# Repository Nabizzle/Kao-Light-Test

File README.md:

# Kao-Light-Test
Scripts for working with the Kao Light Test Model and Hardware

# Table of Contents

* [Getting Started](#getting-started)
  * [Prerequisites](#prerequisites)
* [Running the Code](#running-the-code)
* [Author](#author)
* [Description of Each Script](#description-of-each-script)
  * [panTiltModel.m](#pantiltmodelm)
  
  # Getting Started
  
  As of right now, there is only the modeling code, [panTIltModel.m](#pantiltmodelm), which makes a model of how the laser is controlled. In the future, the code for controlling the Arduino Uno to tilting and panning the read laser mount will be added.
  
  Also included are the Eagle files for making the shield for the Arduino that controlls the servos of the laser mount.
  
  ## Prerequisites
  
  Software:
  
  * [MATLAB 2018 or later](https://www.mathworks.com/help/matlab/) (For the computational model and prefinding tilt and pan angles)
  * [Arduino IDE](https://www.arduino.cc/en/software)
  
  Testing electronics (what is needed is based on the test)
  * Grapevine with micro D to Sub-D cable
  * [Arduino Uno](https://store-usa.arduino.cc/products/arduino-uno-rev3)
  * Arduino Uno Shield

  # Running the Code
  
  When the Arduino code is added, you will need to plug in the shield and the servos and upload the Arduino code to it. You will also need to take the found tilt and pan angles for the grid size that you want and add them to the arduino code. Make sure that there are 4096 tilt values in a single row array.
  Also make sure to plug in the digital output cable from the Grapevine to the shield. This cable sends out the 12 bit digital signal to control for the 4096 angle values and a 13th signal to turn the laser on or off.
  
  # Author

  * **Nabeel Chowdhury** - Initial Creator
  
  # Description of Each Script
  
  ## panTiltModel.m
  Creates a computational model of the laser mount with user definable dimensions. For more information on how the model is made, refer to [this](https://github.com/Nabizzle/Kao-Light-Test/blob/main/docs/supplimentary/Modeling%20Laser%20Mount%20Pan%20and%20Tilt.pdf) supplimentary document.
  The code has 3 modes: debug, finding tilt and pan angles for a grid of points, visualizing the laser hit location of a given command position.
  
  In bebug mode, the laser tries to hit a square grid of points that is as wide as the gird is far away from the laser mount. The distance the mount is from the grid is user definable. The result of the laser mount hitting a 20x20 grid when 200 mm away from the grid is shown below.
  
  The finding angles mode, the user define a recangular grid of points for the model to find tile and pan angles for. This mode also outputs the expected laser hit locations for you to make sure that the code is working correctly.
  
  The final model allows you to set a command position at the top of the code and see that the model is hitting the right grid point.

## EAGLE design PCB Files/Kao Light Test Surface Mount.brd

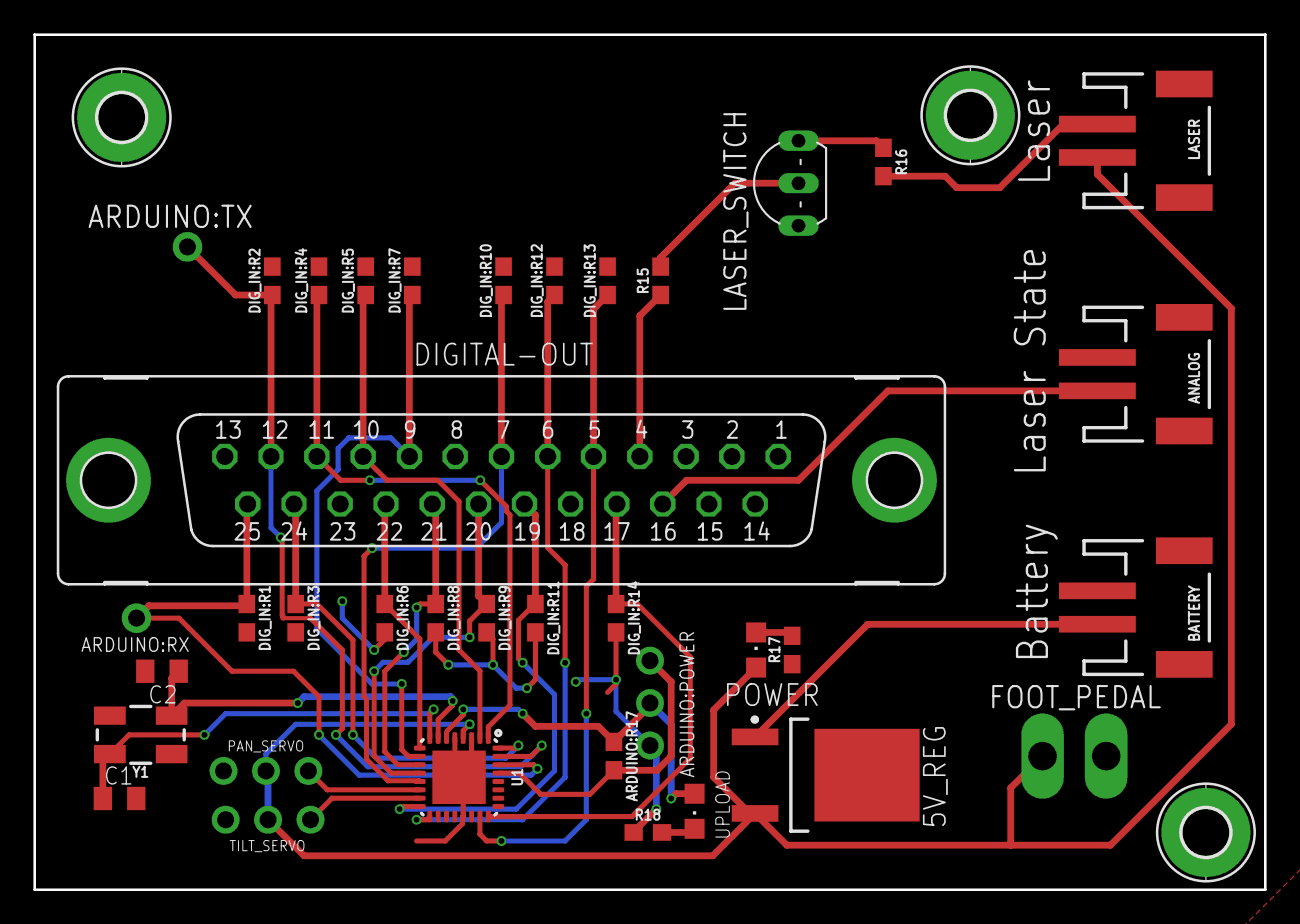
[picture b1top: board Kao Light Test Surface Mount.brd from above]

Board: 2 copper layers, 73.7 x 51.2 mm, 40 parts (0 on the bottom side), 30 nets.

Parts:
5V_REG: UA78M05IKVURG3; KVU0003A_N
ANALOG: JST-2-SMD
ARDUINO:POWER: 1X03-CLEANBIG
ARDUINO:R17: 10k; 0603
ARDUINO:RX: 1X01-CLEANBIG
ARDUINO:TX: 1X01-CLEANBIG
BATTERY: JST-2-SMD
C1, C2: C0805K
DIGITAL-OUT: F25VP
DIG_IN:R1, DIG_IN:R2, DIG_IN:R3, DIG_IN:R4, DIG_IN:R5, DIG_IN:R6, DIG_IN:R7, DIG_IN:R8, DIG_IN:R9, DIG_IN:R10, DIG_IN:R11, DIG_IN:R12, DIG_IN:R13, DIG_IN:R14: 10k; 0603
FOOT_PEDAL: TP2P2-38-17; P2-38-17
H1, H2, H3: MOUNT-PAD-ROUND2.8; 2,8-PAD
LASER: JST-2-SMD
LASER_SWITCH: 2N3904; TO92-EBC-OVAL
PAN_SERVO: 1X03-CLEANBIG
POWER: CHIPLED_0805
R15: 10k; 0603
R16, R17, R18: 220; 0603
TILT_SERVO: 1X03-CLEANBIG
U1: MLF32-PAD
UPLOAD: CHIPLED_0805
Y1: 16MHz; CRYSTAL-SMD-5X3.2-4PAD

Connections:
5VOUT: 5V_REG.3, FOOT_PEDAL.TP-1, LASER.2, PAN_SERVO.2, POWER.A, TILT_SERVO.2, U1.4
BAT+: 5V_REG.1, BATTERY.2
D1: ARDUINO:RX.1, DIGITAL-OUT.25, DIG_IN:R1.1, U1.30
D2: ARDUINO:TX.1, DIGITAL-OUT.12, DIG_IN:R2.1, U1.31
D3: DIGITAL-OUT.24, DIG_IN:R3.1, U1.32
D4: DIGITAL-OUT.11, DIG_IN:R4.1, U1.1
D5: DIGITAL-OUT.10, DIG_IN:R5.1, U1.2
D6: DIGITAL-OUT.22, DIG_IN:R6.1, U1.9
D7: DIGITAL-OUT.9, DIG_IN:R7.1, U1.10
D8: DIGITAL-OUT.21, DIG_IN:R8.1, U1.11
D9: DIGITAL-OUT.20, DIG_IN:R9.1, U1.12
D10: DIGITAL-OUT.7, DIG_IN:R10.1, U1.13
D11: DIGITAL-OUT.19, DIG_IN:R11.1, U1.16
D12: DIGITAL-OUT.6, DIG_IN:R12.1, U1.17
D13: DIGITAL-OUT.5, DIG_IN:R13.1, U1.23
D14: DIGITAL-OUT.17, DIG_IN:R14.1, U1.24
D15: DIGITAL-OUT.4, R15.1
D16: ANALOG.2, DIGITAL-OUT.16
GND: 5V_REG.4, ANALOG.1, ARDUINO:POWER.3, BATTERY.1, C1.2, C2.2, DIGITAL-OUT.1, DIGITAL-OUT.2, DIGITAL-OUT.3, DIGITAL-OUT.8, DIGITAL-OUT.13, DIGITAL-OUT.18, DIGITAL-OUT.23, DIGITAL-OUT.G1, DIGITAL-OUT.G2, DIG_IN:R1.2, DIG_IN:R2.2, DIG_IN:R3.2, DIG_IN:R4.2, DIG_IN:R5.2, DIG_IN:R6.2, DIG_IN:R7.2, DIG_IN:R8.2, DIG_IN:R9.2, DIG_IN:R10.2, DIG_IN:R11.2, DIG_IN:R12.2, DIG_IN:R13.2, DIG_IN:R14.2, FOOT_PEDAL.TP-2, H1.B2,8, H2.B2,8, H3.B2,8, LASER_SWITCH.E, PAN_SERVO.1, R17.1, R18.1, TILT_SERVO.1, U1.3, U1.5, U1.21, U1.PAD
unnamed: C2.1, U1.7, Y1.1
unnamed: LASER_SWITCH.B, R15.2
unnamed: LASER_SWITCH.C, R16.1
unnamed: C1.1, U1.8, Y1.3
unnamed: POWER.C, R17.2
unnamed: LASER.1, R16.2
unnamed: R18.2, UPLOAD.C
PAN: PAN_SERVO.3, U1.14
RESET: ARDUINO:POWER.1, ARDUINO:R17.2, U1.29
TILT: TILT_SERVO.3, U1.15
VIN: ARDUINO:POWER.2, ARDUINO:R17.1, U1.6, UPLOAD.A

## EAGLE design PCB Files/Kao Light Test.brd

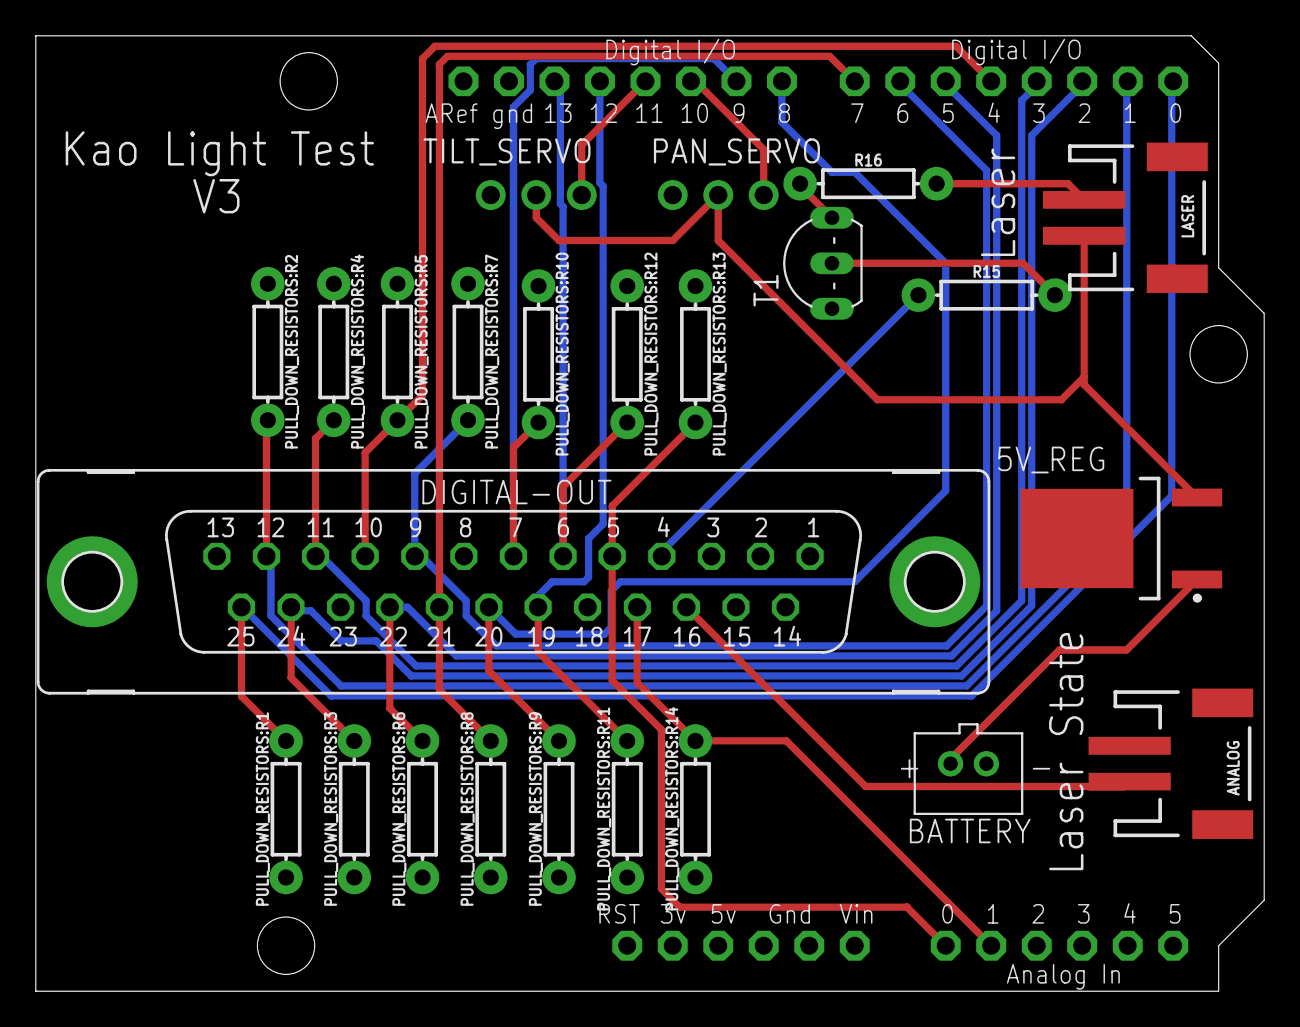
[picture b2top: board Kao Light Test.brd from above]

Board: 2 copper layers, 68.6 x 53.3 mm, 25 parts (0 on the bottom side), 24 nets.

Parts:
5V_REG: UA78M05IKVURG3; KVU0003A_N
ANALOG: JST-2-SMD
BATTERY: JST-PH-2-THM
DIGITAL-OUT: F25VP
LASER: JST-2-SMD
PAN_SERVO: 1X03-CLEANBIG
PULL_DOWN_RESISTORS:R1, PULL_DOWN_RESISTORS:R2, PULL_DOWN_RESISTORS:R3, PULL_DOWN_RESISTORS:R4, PULL_DOWN_RESISTORS:R5, PULL_DOWN_RESISTORS:R6, PULL_DOWN_RESISTORS:R7, PULL_DOWN_RESISTORS:R8, PULL_DOWN_RESISTORS:R9, PULL_DOWN_RESISTORS:R10, PULL_DOWN_RESISTORS:R11, PULL_DOWN_RESISTORS:R12, PULL_DOWN_RESISTORS:R13, PULL_DOWN_RESISTORS:R14: 10k; AXIAL-0.3
R15: 10k; AXIAL-0.3
R16: 220; AXIAL-0.3
T1: 2N2222; TO92-EBC-OVAL
TILT_SERVO: 1X03-CLEANBIG
U$1: ARDUINOUNO; ARDUINO

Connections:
5VOUT: 5V_REG.3, LASER.2, PAN_SERVO.2, TILT_SERVO.2
BAT+: 5V_REG.1, BATTERY.1
D1: DIGITAL-OUT.25, PULL_DOWN_RESISTORS:R1.P$2, U$1.D0
D2: DIGITAL-OUT.12, PULL_DOWN_RESISTORS:R2.P$2, U$1.D1
D3: DIGITAL-OUT.24, PULL_DOWN_RESISTORS:R3.P$2, U$1.D2
D4: DIGITAL-OUT.11, PULL_DOWN_RESISTORS:R4.P$2, U$1.D3
D5: DIGITAL-OUT.10, PULL_DOWN_RESISTORS:R5.P$2, U$1.D4
D6: DIGITAL-OUT.22, PULL_DOWN_RESISTORS:R6.P$2, U$1.D5
D7: DIGITAL-OUT.9, PULL_DOWN_RESISTORS:R7.P$2, U$1.D6
D8: DIGITAL-OUT.21, PULL_DOWN_RESISTORS:R8.P$2, U$1.D7
D9: DIGITAL-OUT.20, PULL_DOWN_RESISTORS:R9.P$2, U$1.D8
D10: DIGITAL-OUT.7, PULL_DOWN_RESISTORS:R10.P$2, U$1.D9
D11: DIGITAL-OUT.19, PULL_DOWN_RESISTORS:R11.P$2, U$1.D12
D12: DIGITAL-OUT.6, PULL_DOWN_RESISTORS:R12.P$2, U$1.D13
D13: DIGITAL-OUT.5, PULL_DOWN_RESISTORS:R13.P$2, U$1.A0
D14: DIGITAL-OUT.17, PULL_DOWN_RESISTORS:R14.P$2, U$1.A1
D15: DIGITAL-OUT.4, R15.P$1
D16: ANALOG.2, DIGITAL-OUT.16
GND_1: 5V_REG.4, ANALOG.1, BATTERY.2, DIGITAL-OUT.1, DIGITAL-OUT.2, DIGITAL-OUT.3, DIGITAL-OUT.8, DIGITAL-OUT.13, DIGITAL-OUT.18, DIGITAL-OUT.23, DIGITAL-OUT.G1, DIGITAL-OUT.G2, PAN_SERVO.1, PULL_DOWN_RESISTORS:R1.P$1, PULL_DOWN_RESISTORS:R2.P$1, PULL_DOWN_RESISTORS:R3.P$1, PULL_DOWN_RESISTORS:R4.P$1, PULL_DOWN_RESISTORS:R5.P$1, PULL_DOWN_RESISTORS:R6.P$1, PULL_DOWN_RESISTORS:R7.P$1, PULL_DOWN_RESISTORS:R8.P$1, PULL_DOWN_RESISTORS:R9.P$1, PULL_DOWN_RESISTORS:R10.P$1, PULL_DOWN_RESISTORS:R11.P$1, PULL_DOWN_RESISTORS:R12.P$1, PULL_DOWN_RESISTORS:R13.P$1, PULL_DOWN_RESISTORS:R14.P$1, T1.E, TILT_SERVO.1, U$1.GND, U$1.GND1
unnamed: R15.P$2, T1.B
unnamed: R16.P$1, T1.C
unnamed: LASER.1, R16.P$2
PAN: PAN_SERVO.3, U$1.D10
TILT: TILT_SERVO.3, U$1.D11

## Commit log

2021-09-11 Adds the initial files
    Adds the .gitignore file and the initial file that compute the correct
    tilt angle when there is no pan.
2021-09-11 feat: Adds code to find pan angle
    Also adds code to record a video testing the angle choices on hitting a
    grid.
2021-09-11 feat: deletes the video writter code
2021-09-11 docs: Adds debug video to docs folder
2021-09-11 feat: Adds debug and find angles flags
    The code now has a debug mode and a mode that finds all of the angles to
    hit a specific size grid with a given resolution
2021-09-11 docs: Adds files to describing tilt and pan calc
    Makes a LaTeX doc with figures to describe how the tilt and pan angles
    are found.
2021-09-11 feat: Adds functionality to code that finds angles
    The code how finds angles for a 5mm rectangular grid and also has code
    that outputs the locations where the model expects the laser to hit the
    target.
2021-09-12 docs: Updated suplimentary doc about modeling
2021-09-12 fix: fixes gitignore file
    The gitignore file was named incorrectly
2021-09-12 feat: Adds switch case to modes
    Eliminates the if else statements in favor of a switch statement. NOTE,
    there is still a bug in mode 2 for finidng angles
2021-09-12 fix: Fixed syntax errors
    Ran through each mode and fixed errors that came up. Also, fixed a bug
    where the find angles code did not reach the right most points.
2021-09-12 docs: Adds a gif version of the debug video
2021-09-12 Rename panTIltModel.m to panTiltModel.m
2021-09-12 docs: Adds Images of Arduino Shield
2021-09-12 docs: Creates initial ReadMe
2021-09-12 docs: Moves ReadMe to docs folder
2021-09-12 fix: fixes the end of the grid X array for loop
2021-09-12 feat: Updates .gitignore for Eagle Files
2021-09-12 move: Moves code to a Code directory
2021-09-12 docs: Adds an SVG file for the target grid
    The grid is colored in case you want to laser cut it and engrave the
    grid
2021-09-12 feat: Adds the Eagle files
2022-03-26 feat: Creates a debug script for the foot pedal
    Closes #5
2022-03-26 feat: Convert the graph to volts
2022-03-26 feat; Adds a debug script for the digital output
    Closes #6
2022-03-26 feat: Adds gitingore file for Matlab files
2022-03-26 feat: Adds script to convert digital signal to num
    Adds a debug script for finding the base 10 number from the input
    digital signals. NOTE that the first two outputs are always set to their
    values since they are also used for the serial monitor. They should work
    when commanding the servos.
    Closes #2
2022-03-26 fix: Changes the model to only have 400 points
    The lowered number of points to to account for the arduino's memory
2022-03-26 feat: Creates the script to control the servos
    Adds an arduino script to take in the digital outputs of the Grapevine
    and move the servo to desired positions based on the computational model
    Closes #7
2022-03-26 fix: Changes the model to fit the real dimensions
    Changes the model and the arrays of found positions to match the real
    dimensions of the testing setup
2022-03-26 feat: Creates app and servo angle finder function
    Crates the code to find the servo angles and lets the experimentor
    examine them. Also outputs the variables to the workspace in case the
    user wants to copy over the angles to the arduino.
    Closes #8
2022-03-26 feat: Adds a function to test the laser
    Adds a laser toggle and a function to determine where the laser will hit
    with its various tilt angles
2022-03-26 feat: Adds a function to pan the laser at tilt
    Adds a function to pan the laser at the current tilt angle.
    Closes #1
2022-03-27 feat: Adds experiment recording script
    Adds the script to iterate through each point along the desired tilt
    angle. The script also take in the number of repeated trials from a GUI
    element and saves out the data for analysis afterwards.
    Closes #3
2022-03-28 feat: Adds Test stop and Validates code
    Adds a lamp to indicate when the test is running, a stop test button,
    and validates that all parts of the test work at least without a
    subject. The code also now saves out the servo angles used for the test
    which it needed to previously, but I forgot to add.
    Closes #10
2022-03-28 fix: Turns on the laser in the laser sweep code
    The laser did not actually turn on in the laser sweep code. Also
    shortens the time between each pan angle in the laser sweep.
2022-03-28 docs: Adds an image of the testing app.
2022-03-28 fix: Adds a white background the the app image
2022-03-28 docs: Updates ReadMe to be up to date with v2.1.1
2022-03-29 fix: Addresses error in the main test
    The laser didn't turn on in the test since the laser state indicator
    would turn off the parallel port. Now, both turn on together.
2022-03-29 fix: Removes the displayed output from the sweep
2022-03-31 feat: Adds the data analysis code
    Adds code to analyze the prelim data. This code needs to be refined and
    added to the app.
    Closes #4
2022-03-31 docs: Updates ReadMe with data analysis scripts
    Also fixes alphabetical order of script descriptions
2022-09-15 feat: Saves a list of test angles
    App now allows the user to save a list of tilt angles for the test as
    well as manually edit or delete elements of the list. The current code
    allows duplicate entries, but that could be eliminated if undesired.
    Closes #14 issue.
2022-09-19 feat: updates PCB
    Adds changes from Issue #9
2022-09-19 BREAKING CHANGE feat: Grapevine to controls angle
    Changes code so that the first seven digital outputs of the Grapevine
    control the pan angle of the laser and the last 5 digital outputs
    control the tilt angle. The rest of the functions are updated
    accordingly. For example all code to calculate angles was been deleted
    and the functions that refered to the calculated angles have been
    updated to use the new angle formats. Also added a Guage for test
2022-09-19 feat: Updates the look of the GUI
    Makes the laser toggle a toggle switch and updates the start button
    color
2022-09-19 chore: Updates look of Gui
    Updates the tick labels of the pan and tilt sliders to be more logical
    numbers.
2022-09-20 feat: Grapevine controls pan and tilt angles
    The arduino takes the 12 digital inputs from the Grapevine and converts
    the first 7 into 128 different pan angles and the last 5 inputs as 32
    different tilt angles. The pan and tilt angles range around the center
    of their range of motion.
    Closes #11 and closes #13 issues.
2022-09-21 docs: Updates ReadMe with the changes to the Gui
2022-09-21 fix: Adjusts the pan and tilt sliders numbering
    The sliders and table now accurately show the pan and tilt angles in
    degrees. Extra variables were also eliminated and the GUI image in the
    ReadMe was updated.
2022-09-21 chore: Updates the code for new laser state output
    Switches the output from the first SMA to the 14th output of the microD
    connector
2022-09-21 feat: Improves the look of the PCB
    Improves the naming and clenliness of the PCB
2022-09-21 docs: Updates the ReadMe with the new PCB design.
2022-09-21 docs: Adds name of test to PCB
2022-09-21 feat: Grounds the Cable's housing.
    Also updates the images in the ReadMe
2022-09-22 docs: Adds note to the ReadMe on flashing scripts
    Adds a note that the arduino shield must be disconnected from the
    arduino when flashing a new script as the pull-down resistors on digital
    inputs 0 and 1 prevent the upload process from occurring. This is also
    why the Serial monitor does not work properly with the shield for these
    pins.
2022-09-22 docs: Updates the PCB and ReadMe to be clearer
    The PCB was updated so that the servos are labeled as what they are
    instead of as numbers. One resistor was also updated and all other
    digital grounds were connected to the ground plane.
2022-09-22 fix: Corrects logic in code
    Corrects how the arduino interprets digital inputs from the grapevine.
2022-09-22 feat: Tests and corrects errors in test
    Tests the code on the Grapevine. Testing revealed that the resistor
    connected between the laser and the transistor's collector needed to be
    the original value of 220 ohms and all of the pull-down resistors need
    to be at least 10k Ohms or higher.
2022-09-22 docs: Updates PCB and ReadMe based on testing
    Updates the PCB resistor values and images of the PCB based on the
    testing done in the previous commit.
2022-09-23 fix: corrects typos
2022-09-24 feat: Adds two more digital outputs to tilt angles
    Updates the GUI, Arduino code, and PCB for two more digital outputs to
    up the tilt angles from 32 to 128 angles. Also addresses small fixes.
    Closes #18 issue
2022-09-24 feat: Adds a surface mount version of the PCB
    Adds a version of the PCB with almost all surface mount components and
    an integrated Amega328P as a replacement of the arduino on the board.
2022-09-25 feat: Adds status LEDs and Logo
    Adds LEDs to indicate power from either the programming arduino's 5V
    output or from the 5V regulator on the PCB. The LEDs should be different
    colors and are labeled on the board. The logo is of the iSens logo
2022-09-26 feat: Adds a clickable gird to select angles
    Adds a grid to select the pan and tilt angles from. Also, when angles
    are saved and deleted from the table, they show up as red points on the
    grid.
    Closes #19 issue
2022-09-28 fix: Addresses small bugs in code

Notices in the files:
parts and their libraries:
SparkFun-Connectors: Licensing: Creative Commons ShareAlike 4.0 International - https://creativecommons.org/licenses/by-sa/4.0
COPYRIGHT: Copyright (C) 2021 Ultra Librarian. All rights reserved.
